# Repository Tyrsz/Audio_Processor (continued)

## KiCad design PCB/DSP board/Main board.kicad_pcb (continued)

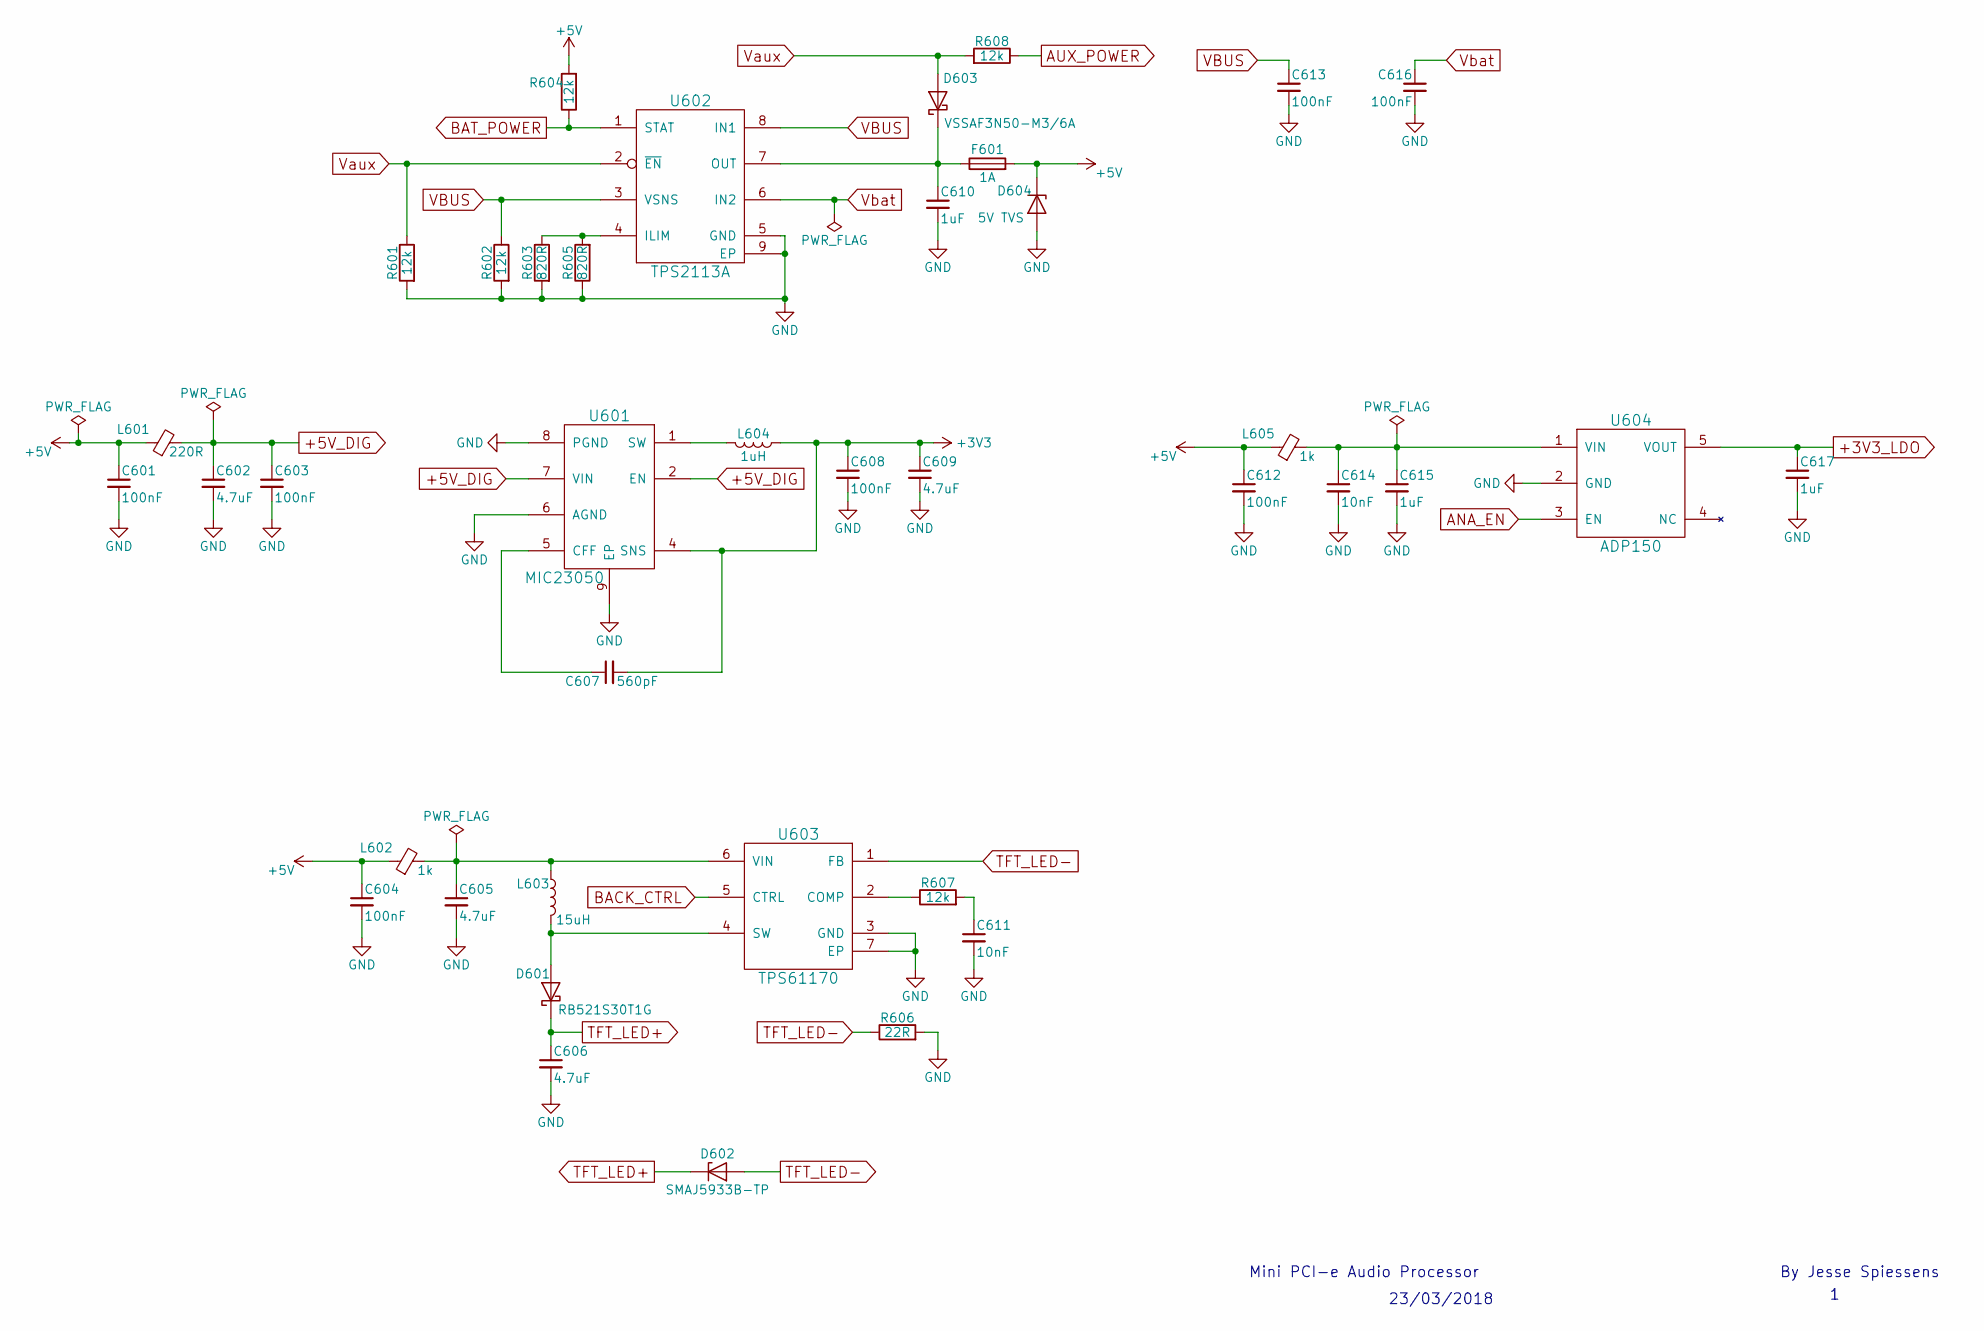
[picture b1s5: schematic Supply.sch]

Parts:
C601, C603, C604, C608, C612, C613, C616: 100nF; C_0603
C602, C605, C609: 4.7uF; C_0805
C606: 4.7uF; C_1206
C607: 560pF; C_0603
C610, C615, C617: 1uF; C_0603
C611, C614: 10nF; C_0603
D601: RB521S30T1G; D_SOD-523
D602: SMAJ5933B-TP; D_SMA
D603: VSSAF3N50-M3/6A; D_SMA
D604: 5V TVS; SOD-323F-2
F601: 1A; R_0603
L601: 220R; L_0603
L602, L605: 1k; L_0603
L603: 15uH; L_0805
L604: 1uH; L_0805
R601, R602, R604, R607, R608: 12k; R_0603
R603, R605: 820R; R_0603
R606: 22R; R_0805
U601: MIC23050; DFN-8-1EP_2x2mm_Pitch0.5mm
U602: TPS2113A; DFN-8-1EP_3x3mm_Pitch0.65mm
U603: TPS61170; DFN-6-1EP_2x2mm_Pitch0.65mm
U604: ADP150; TSOP-5_1.65x3.05mm_Pitch0.95mm

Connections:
+3V3: C607.2, C608.1, C609.1, L604.1, U601.4 (SNS); also elsewhere on the board
+3V3_LDO: C617.1, U604.5 (VOUT); also elsewhere on the board
+5V: C601.1, C604.1, C612.1, D604.1 (K), F601.2, L601.1, L602.1, L605.1, R604.2; also elsewhere on the board
+5V_DIG: C602.1, C603.1, L601.2, U601.2 (EN), U601.7 (VIN)
ANA_EN: U604.3 (EN); also elsewhere on the board
AUX_POWER: R608.1; also elsewhere on the board
BACK_CTRL: U603.5 (CTRL); also elsewhere on the board
BAT_POWER: R604.1, U602.1 (STAT); also elsewhere on the board
GND: C601.2, C602.2, C603.2, C604.2, C605.2, C606.2, C608.2, C609.2, C610.2, C611.2, C612.2, C613.2, C614.2, C615.2, C616.2, C617.2, D604.2 (A), R601.2, R602.2, R603.2, R605.1, R606.2, U601.6 (AGND), U601.8 (PGND), U601.9 (EP), U602.5 (GND), U602.9 (EP), U603.3 (GND), U603.7 (EP), U604.2 (GND); also elsewhere on the board
unnamed: C605.1, L602.2, L603.1, U603.6 (VIN)
unnamed: C607.1, U601.5 (CFF)
unnamed: C610.1, D603.1 (K), F601.1, U602.7 (OUT)
unnamed: C611.1, R607.2
unnamed: C614.1, C615.1, L605.2, U604.1 (VIN)
unnamed: D601.2 (A), L603.2, U603.4 (SW)
unnamed: L604.2, U601.1 (SW)
unnamed: R603.1, R605.2, U602.4 (ILIM)
unnamed: R607.1, U603.2 (COMP)
TFT_LED+: C606.1, D601.1 (K), D602.1 (K); also elsewhere on the board
TFT_LED-: D602.2 (A), R606.1, U603.1 (FB); also elsewhere on the board
VBUS: C613.1, R602.1, U602.3 (VSNS), U602.8 (IN1); also elsewhere on the board
Vaux: D603.2 (A), R601.1, R608.2, U602.2 (~EN); also elsewhere on the board
Vbat: C616.1, U602.6 (IN2); also elsewhere on the board

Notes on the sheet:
23/03/2018
Mini PCI-e Audio Processor
By Jesse Spiessens

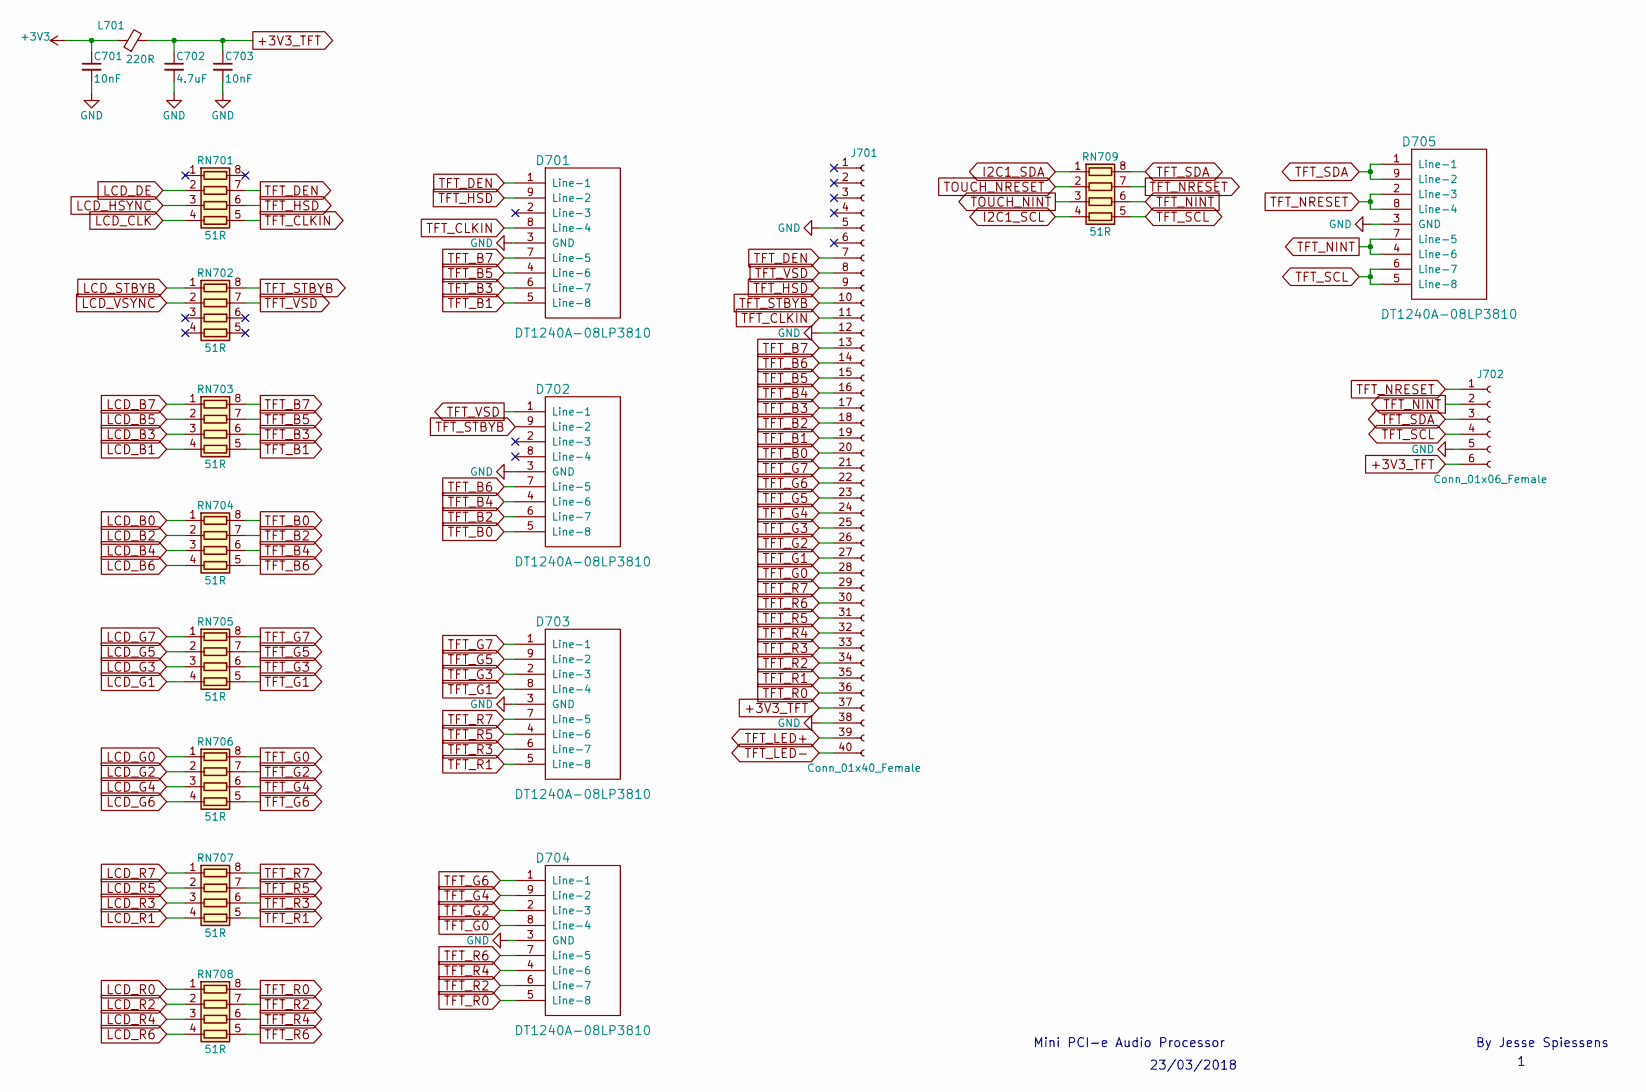
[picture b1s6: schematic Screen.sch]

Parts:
C701, C703: 10nF; C_0603
C702: 4.7uF; C_0805
D701, D702, D703, D704, D705: DT1240A-08LP3810; U-DFN3810-9
J701: Conn_01x40_Female; 78127-1408
J702: Conn_01x06_Female; 52808-0671
L701: 220R; L_0603
RN701, RN702, RN703, RN704, RN705, RN706, RN707, RN708, RN709: 51R; 0603_RN4

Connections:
+3V3: C701.1, L701.1; also elsewhere on the board
+3V3_TFT: C702.1, C703.1, J701.37, J702.6, L701.2
GND: C701.2, C702.2, C703.2, D701.3 (GND), D702.3 (GND), D703.3 (GND), D704.3 (GND), D705.3 (GND), J701.5, J701.12, J701.38, J702.5; also elsewhere on the board
I2C1_SCL: RN709.4 (R4.1); also elsewhere on the board
I2C1_SDA: RN709.1 (R1.1); also elsewhere on the board
LCD_B0: RN704.1 (R1.1); also elsewhere on the board
LCD_B1: RN703.4 (R4.1); also elsewhere on the board
LCD_B2: RN704.2 (R2.1); also elsewhere on the board
LCD_B3: RN703.3 (R3.1); also elsewhere on the board
LCD_B4: RN704.3 (R3.1); also elsewhere on the board
LCD_B5: RN703.2 (R2.1); also elsewhere on the board
LCD_B6: RN704.4 (R4.1); also elsewhere on the board
LCD_B7: RN703.1 (R1.1); also elsewhere on the board
LCD_CLK: RN701.4 (R4.1); also elsewhere on the board
LCD_DE: RN701.2 (R2.1); also elsewhere on the board
LCD_G0: RN706.1 (R1.1); also elsewhere on the board
LCD_G1: RN705.4 (R4.1); also elsewhere on the board
LCD_G2: RN706.2 (R2.1); also elsewhere on the board
LCD_G3: RN705.3 (R3.1); also elsewhere on the board
LCD_G4: RN706.3 (R3.1); also elsewhere on the board
LCD_G5: RN705.2 (R2.1); also elsewhere on the board
LCD_G6: RN706.4 (R4.1); also elsewhere on the board
LCD_G7: RN705.1 (R1.1); also elsewhere on the board
LCD_HSYNC: RN701.3 (R3.1); also elsewhere on the board
LCD_R0: RN708.1 (R1.1); also elsewhere on the board
LCD_R1: RN707.4 (R4.1); also elsewhere on the board
LCD_R2: RN708.2 (R2.1); also elsewhere on the board
LCD_R3: RN707.3 (R3.1); also elsewhere on the board
LCD_R4: RN708.3 (R3.1); also elsewhere on the board
LCD_R5: RN707.2 (R2.1); also elsewhere on the board
LCD_R6: RN708.4 (R4.1); also elsewhere on the board
LCD_R7: RN707.1 (R1.1); also elsewhere on the board
LCD_STBYB: RN702.1 (R1.1); also elsewhere on the board
LCD_VSYNC: RN702.2 (R2.1); also elsewhere on the board
TFT_B0: D702.5 (Line-8), J701.20, RN704.8 (R1.2)
TFT_B1: D701.5 (Line-8), J701.19, RN703.5 (R4.2)
TFT_B2: D702.6 (Line-7), J701.18, RN704.7 (R2.2)
TFT_B3: D701.6 (Line-7), J701.17, RN703.6 (R3.2)
TFT_B4: D702.4 (Line-6), J701.16, RN704.6 (R3.2)
TFT_B5: D701.4 (Line-6), J701.15, RN703.7 (R2.2)
TFT_B6: D702.7 (Line-5), J701.14, RN704.5 (R4.2)
TFT_B7: D701.7 (Line-5), J701.13, RN703.8 (R1.2)
TFT_CLKIN: D701.8 (Line-4), J701.11, RN701.5 (R4.2)
TFT_DEN: D701.1 (Line-1), J701.7, RN701.7 (R2.2)
TFT_G0: D704.8 (Line-4), J701.28, RN706.8 (R1.2)
TFT_G1: D703.8 (Line-4), J701.27, RN705.5 (R4.2)
TFT_G2: D704.2 (Line-3), J701.26, RN706.7 (R2.2)
TFT_G3: D703.2 (Line-3), J701.25, RN705.6 (R3.2)
TFT_G4: D704.9 (Line-2), J701.24, RN706.6 (R3.2)
TFT_G5: D703.9 (Line-2), J701.23, RN705.7 (R2.2)
TFT_G6: D704.1 (Line-1), J701.22, RN706.5 (R4.2)
TFT_G7: D703.1 (Line-1), J701.21, RN705.8 (R1.2)
TFT_HSD: D701.9 (Line-2), J701.9, RN701.6 (R3.2)
TFT_LED+: J701.39; also elsewhere on the board
TFT_LED-: J701.40; also elsewhere on the board
TFT_NINT: D705.4 (Line-6), D705.7 (Line-5), J702.2, RN709.6 (R3.2)
TFT_NRESET: D705.2 (Line-3), D705.8 (Line-4), J702.1, RN709.7 (R2.2)
TFT_R0: D704.5 (Line-8), J701.36, RN708.8 (R1.2)
TFT_R1: D703.5 (Line-8), J701.35, RN707.5 (R4.2)
TFT_R2: D704.6 (Line-7), J701.34, RN708.7 (R2.2)
TFT_R3: D703.6 (Line-7), J701.33, RN707.6 (R3.2)
TFT_R4: D704.4 (Line-6), J701.32, RN708.6 (R3.2)
TFT_R5: D703.4 (Line-6), J701.31, RN707.7 (R2.2)
TFT_R6: D704.7 (Line-5), J701.30, RN708.5 (R4.2)
TFT_R7: D703.7 (Line-5), J701.29, RN707.8 (R1.2)
TFT_SCL: D705.5 (Line-8), D705.6 (Line-7), J702.4, RN709.5 (R4.2)
TFT_SDA: D705.1 (Line-1), D705.9 (Line-2), J702.3, RN709.8 (R1.2)
TFT_STBYB: D702.9 (Line-2), J701.10, RN702.8 (R1.2)
TFT_VSD: D702.1 (Line-1), J701.8, RN702.7 (R2.2)
TOUCH_NINT: RN709.3 (R3.1); also elsewhere on the board
TOUCH_NRESET: RN709.2 (R2.1); also elsewhere on the board

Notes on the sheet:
23/03/2018
Mini PCI-e Audio Processor
By Jesse Spiessens

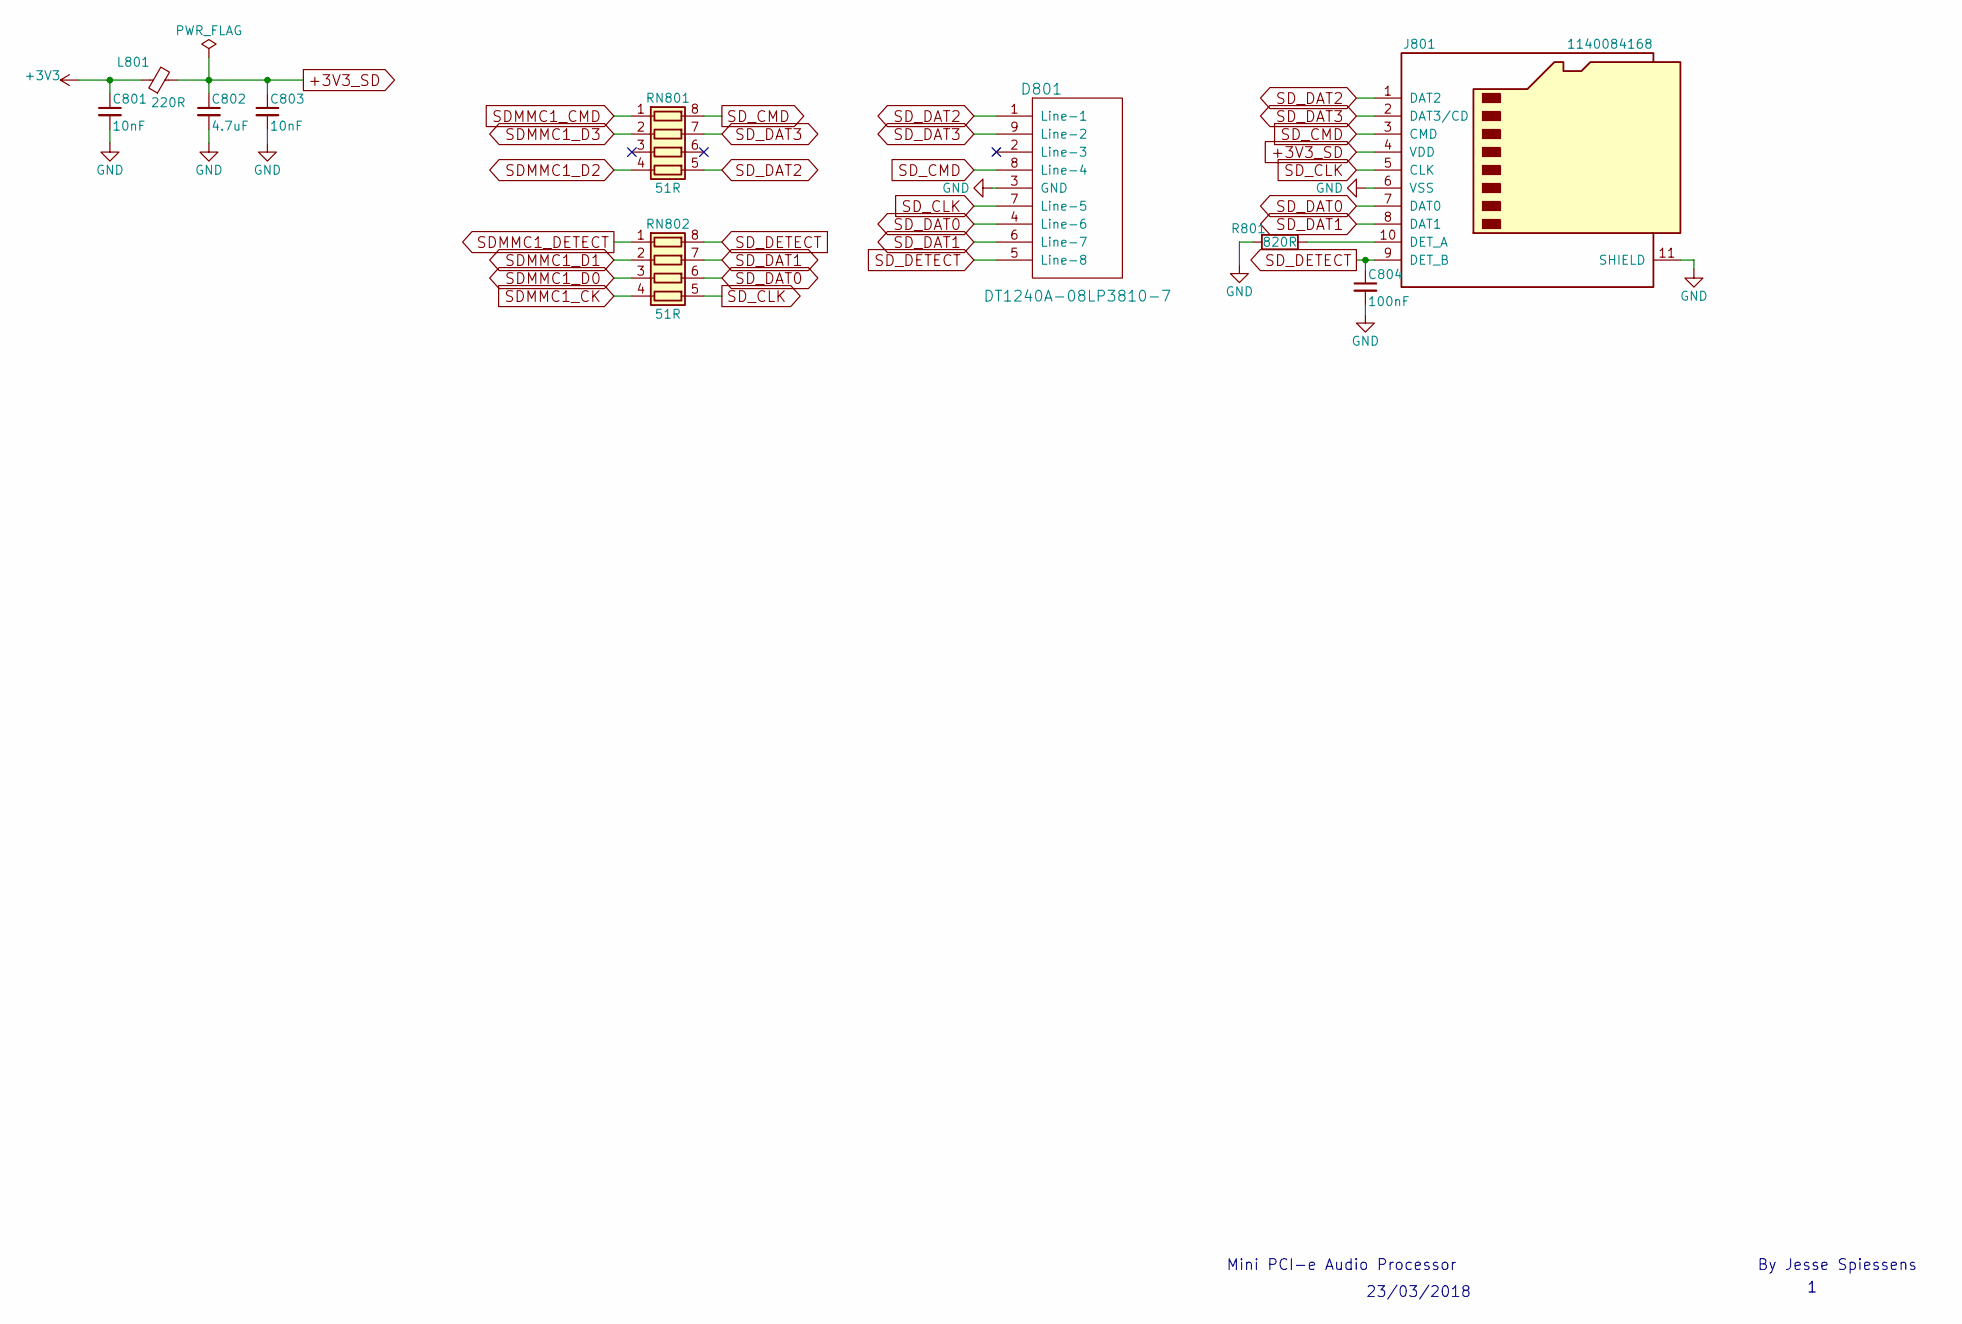
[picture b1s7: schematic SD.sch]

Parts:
C801, C803: 10nF; C_0603
C802: 4.7uF; C_0805
C804: 100nF; C_0603
D801: DT1240A-08LP3810-7; U-DFN3810-9
J801: 1140084168
L801: 220R; L_0603
R801: 820R; R_0603
RN801, RN802: 51R; 0603_RN4

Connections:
+3V3: C801.1, L801.1; also elsewhere on the board
+3V3_SD: C802.1, C803.1, J801.4 (VDD), L801.2
GND: C801.2, C802.2, C803.2, C804.2, D801.3 (GND), J801.6 (VSS), J801.11 (SHIELD), R801.2; also elsewhere on the board
unnamed: J801.10 (DET_A), R801.1
SDMMC1_CK: RN802.4 (R4.1); also elsewhere on the board
SDMMC1_CMD: RN801.1 (R1.1); also elsewhere on the board
SDMMC1_D0: RN802.3 (R3.1); also elsewhere on the board
SDMMC1_D1: RN802.2 (R2.1); also elsewhere on the board
SDMMC1_D2: RN801.4 (R4.1); also elsewhere on the board
SDMMC1_D3: RN801.2 (R2.1); also elsewhere on the board
SDMMC1_DETECT: RN802.1 (R1.1); also elsewhere on the board
SD_CLK: D801.7 (Line-5), J801.5 (CLK), RN802.5 (R4.2)
SD_CMD: D801.8 (Line-4), J801.3 (CMD), RN801.8 (R1.2)
SD_DAT0: D801.4 (Line-6), J801.7 (DAT0), RN802.6 (R3.2)
SD_DAT1: D801.6 (Line-7), J801.8 (DAT1), RN802.7 (R2.2)
SD_DAT2: D801.1 (Line-1), J801.1 (DAT2), RN801.5 (R4.2)
SD_DAT3: D801.9 (Line-2), J801.2 (DAT3/CD), RN801.7 (R2.2)
SD_DETECT: C804.1, D801.5 (Line-8), J801.9 (DET_B), RN802.8 (R1.2)

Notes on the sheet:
23/03/2018
Mini PCI-e Audio Processor
By Jesse Spiessens

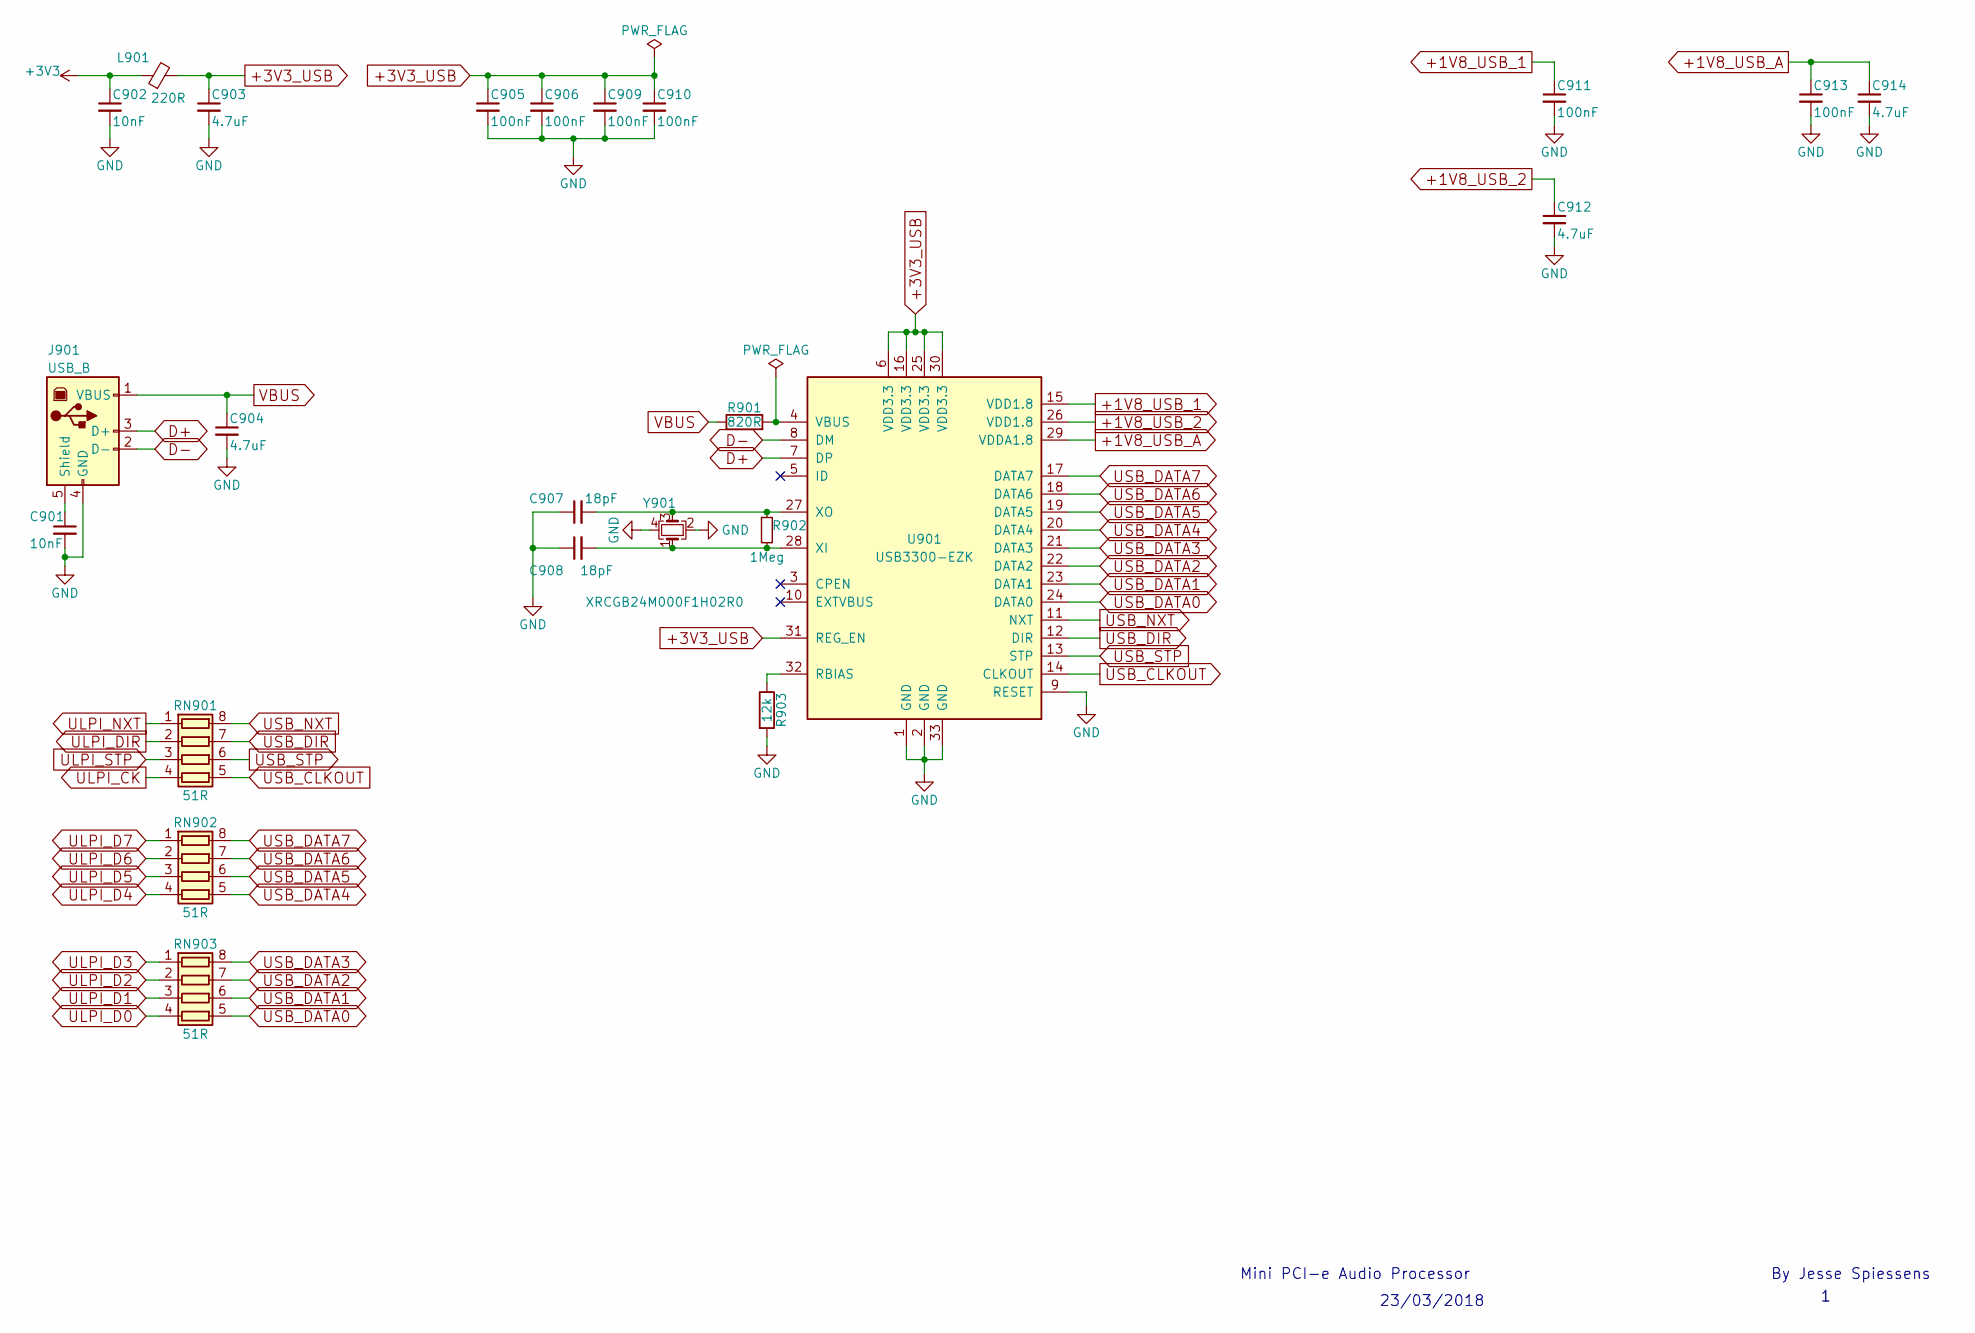
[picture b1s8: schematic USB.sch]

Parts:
C901, C902: 10nF; C_0603
C903, C904, C912, C914: 4.7uF; C_0805
C905, C906, C909, C910, C911, C913: 100nF; C_0603
C907, C908: 18pF; C_0603
J901: USB_B; USB_B_2.0
L901: 220R; L_0603
R901: 820R; R_0603
R902: 1Meg; R_0603
R903: 12k; R_0603
RN901, RN902, RN903: 51R; 0603_RN4
U901: USB3300-EZK; QFN-32-1EP_5x5mm_Pitch0.5mm
Y901: XRCGB24M000F1H02R0; Crystal_SMD_2016-4pin_2.0x1.6mm

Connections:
+1V8_USB_1: C911.1, U901.15 (VDD1.8)
+1V8_USB_2: C912.1, U901.26 (VDD1.8)
+1V8_USB_A: C913.1, C914.1, U901.29 (VDDA1.8)
+3V3: C902.1, L901.1; also elsewhere on the board
+3V3_USB: C903.1, C905.1, C906.1, C909.1, C910.1, L901.2, U901.6 (VDD3.3), U901.16 (VDD3.3), U901.25 (VDD3.3), U901.30 (VDD3.3), U901.31 (REG_EN)
D+: J901.3 (D+), U901.7 (DP); also elsewhere on the board
D-: J901.2 (D-), U901.8 (DM); also elsewhere on the board
GND: C901.2, C902.2, C903.2, C904.2, C905.2, C906.2, C907.1, C908.1, C909.2, C910.2, C911.2, C912.2, C913.2, C914.2, J901.4 (GND), R903.2, U901.1 (GND), U901.2 (GND), U901.9 (RESET), U901.33 (GND), Y901.2, Y901.4; also elsewhere on the board
unnamed: C901.1, J901.5 (Shield)
unnamed: C907.2, R902.1, U901.27 (XO), Y901.3
unnamed: C908.2, R902.2, U901.28 (XI), Y901.1
unnamed: R901.2, U901.4 (VBUS)
unnamed: R903.1, U901.32 (RBIAS)
ULPI_CK: RN901.4 (R4.1); also elsewhere on the board
ULPI_D0: RN903.4 (R4.1); also elsewhere on the board
ULPI_D1: RN903.3 (R3.1); also elsewhere on the board
ULPI_D2: RN903.2 (R2.1); also elsewhere on the board
ULPI_D3: RN903.1 (R1.1); also elsewhere on the board
ULPI_D4: RN902.4 (R4.1); also elsewhere on the board
ULPI_D5: RN902.3 (R3.1); also elsewhere on the board
ULPI_D6: RN902.2 (R2.1); also elsewhere on the board
ULPI_D7: RN902.1 (R1.1); also elsewhere on the board
ULPI_DIR: RN901.2 (R2.1); also elsewhere on the board
ULPI_NXT: RN901.1 (R1.1); also elsewhere on the board
ULPI_STP: RN901.3 (R3.1); also elsewhere on the board
USB_CLKOUT: RN901.5 (R4.2), U901.14 (CLKOUT)
USB_DATA0: RN903.5 (R4.2), U901.24 (DATA0)
USB_DATA1: RN903.6 (R3.2), U901.23 (DATA1)
USB_DATA2: RN903.7 (R2.2), U901.22 (DATA2)
USB_DATA3: RN903.8 (R1.2), U901.21 (DATA3)
USB_DATA4: RN902.5 (R4.2), U901.20 (DATA4)
USB_DATA5: RN902.6 (R3.2), U901.19 (DATA5)
USB_DATA6: RN902.7 (R2.2), U901.18 (DATA6)
USB_DATA7: RN902.8 (R1.2), U901.17 (DATA7)
USB_DIR: RN901.7 (R2.2), U901.12 (DIR)
USB_NXT: RN901.8 (R1.2), U901.11 (NXT)
USB_STP: RN901.6 (R3.2), U901.13 (STP)
VBUS: C904.1, J901.1 (VBUS), R901.1; also elsewhere on the board

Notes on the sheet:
23/03/2018
Mini PCI-e Audio Processor
By Jesse Spiessens

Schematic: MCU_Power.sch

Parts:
C301, C304, C305, C306, C311, C312, C313, C314, C319, C320, C321, C326, C327, C332, C333, C334: 1uF; C_0603
C302, C307, C308, C309, C315, C316, C317, C318, C322, C323, C324, C329, C330, C335, C336, C337: 10nF; C_0603
C303, C331: 100nF; C_0603
C310: 4.7uF; C_0805
C338, C339: 2.2uF; C_0603
L301: 220R; L_0603
L302: 1k; L_0603
U201: STM32H743II; LQFP-176_24x24mm_Pitch0.5mm

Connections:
+3V3: C301.1, C302.1, C303.1, L301.1, L302.1; also elsewhere on the board
+3V3_MCU: C304.1, C305.1, C306.1, C307.1, C308.1, C309.1, C310.1, C312.1, C313.1, C314.1, C316.1, C317.1, C318.1, C319.1, C320.1, C321.1, C322.1, C323.1, C324.1, C326.1, C327.1, C329.1, C330.1, C331.1, C332.1, C333.1, C334.1, C335.1, C336.1, C337.1, L301.2, U201.15 (VDD), U201.23 (VDD), U201.36 (VDD), U201.49 (VDD), U201.62 (VDD), U201.72 (VDD), U201.82 (VDD), U201.91 (VDD), U201.103 (VDD), U201.114 (VDD33USB), U201.127 (VDD), U201.136 (VDD), U201.149 (VDD), U201.159 (VDD), U201.172 (VDD); also elsewhere on the board
GND: C301.2, C302.2, C303.2, C304.2, C305.2, C306.2, C307.2, C308.2, C309.2, C310.2, C311.2, C312.2, C313.2, C314.2, C315.2, C316.2, C317.2, C318.2, C319.2, C320.2, C321.2, C322.2, C323.2, C324.2, C326.2, C327.2, C329.2, C330.2, C331.2, C332.2, C333.2, C334.2, C335.2, C336.2, C337.2, C338.2, C339.2, U201.14 (VSS), U201.22 (VSS), U201.37 (VSSA), U201.48 (VSS), U201.61 (VSS), U201.71 (VSS), U201.90 (VSS), U201.102 (VSS), U201.113 (VSS), U201.126 (VSS), U201.135 (VSS), U201.148 (VSS), U201.158 (VSS); also elsewhere on the board
unnamed: C311.1, C315.1, L302.2, U201.38 (VREF+), U201.39 (VDDA)
unnamed: C338.1, U201.125 (VCAP2)
unnamed: C339.1, U201.81 (VCAP1)

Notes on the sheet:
23/03/2018
Mini PCI-e Audio Processor
By Jesse Spiessens

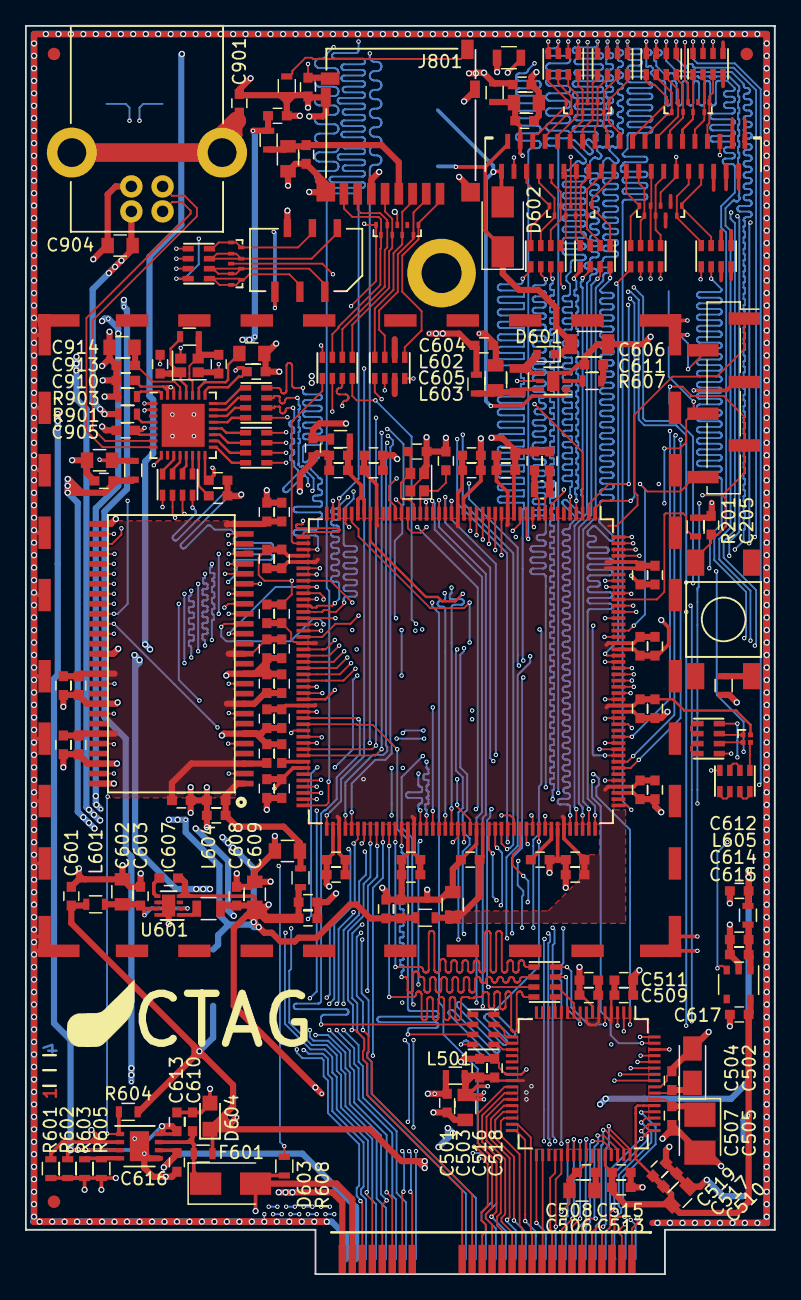
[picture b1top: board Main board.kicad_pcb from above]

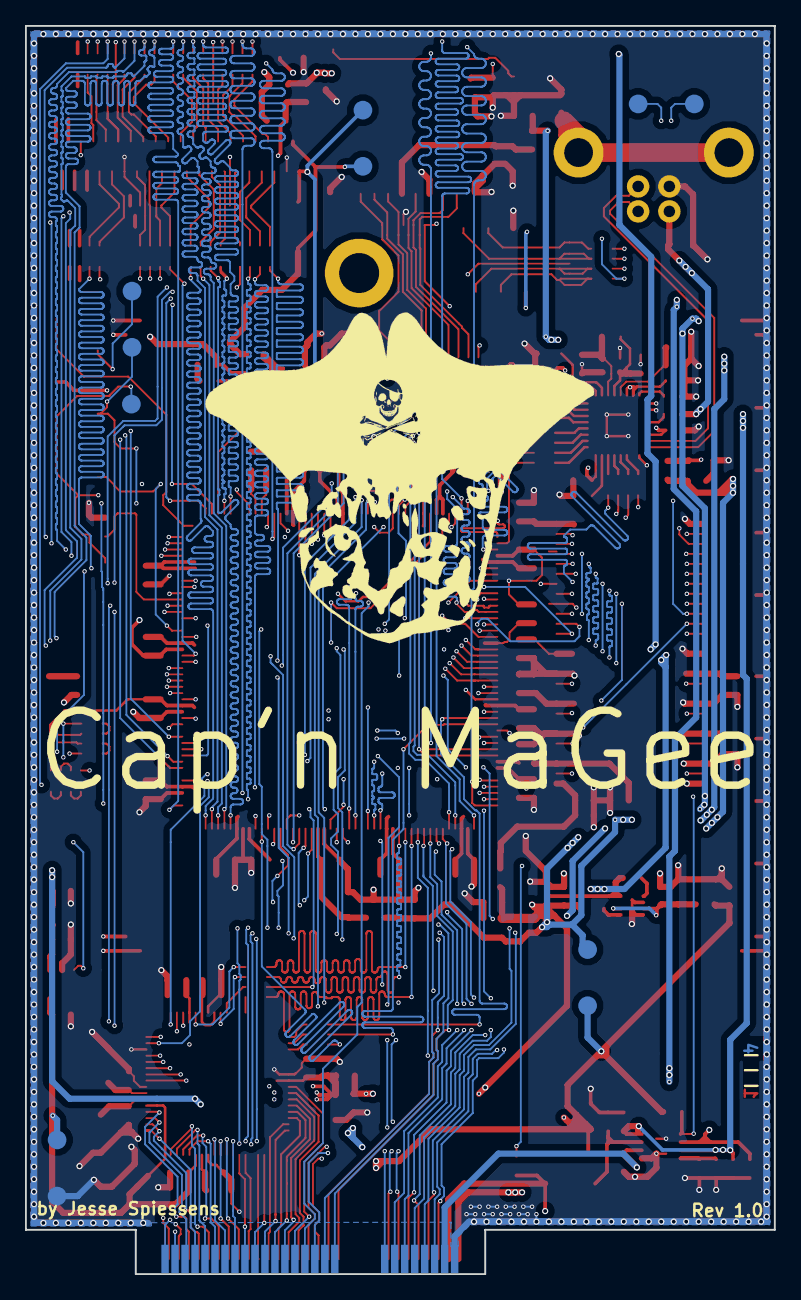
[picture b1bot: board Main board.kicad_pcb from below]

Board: 4 copper layers, 60.0 x 100.0 mm, 202 parts (11 on the bottom side), 269 nets.

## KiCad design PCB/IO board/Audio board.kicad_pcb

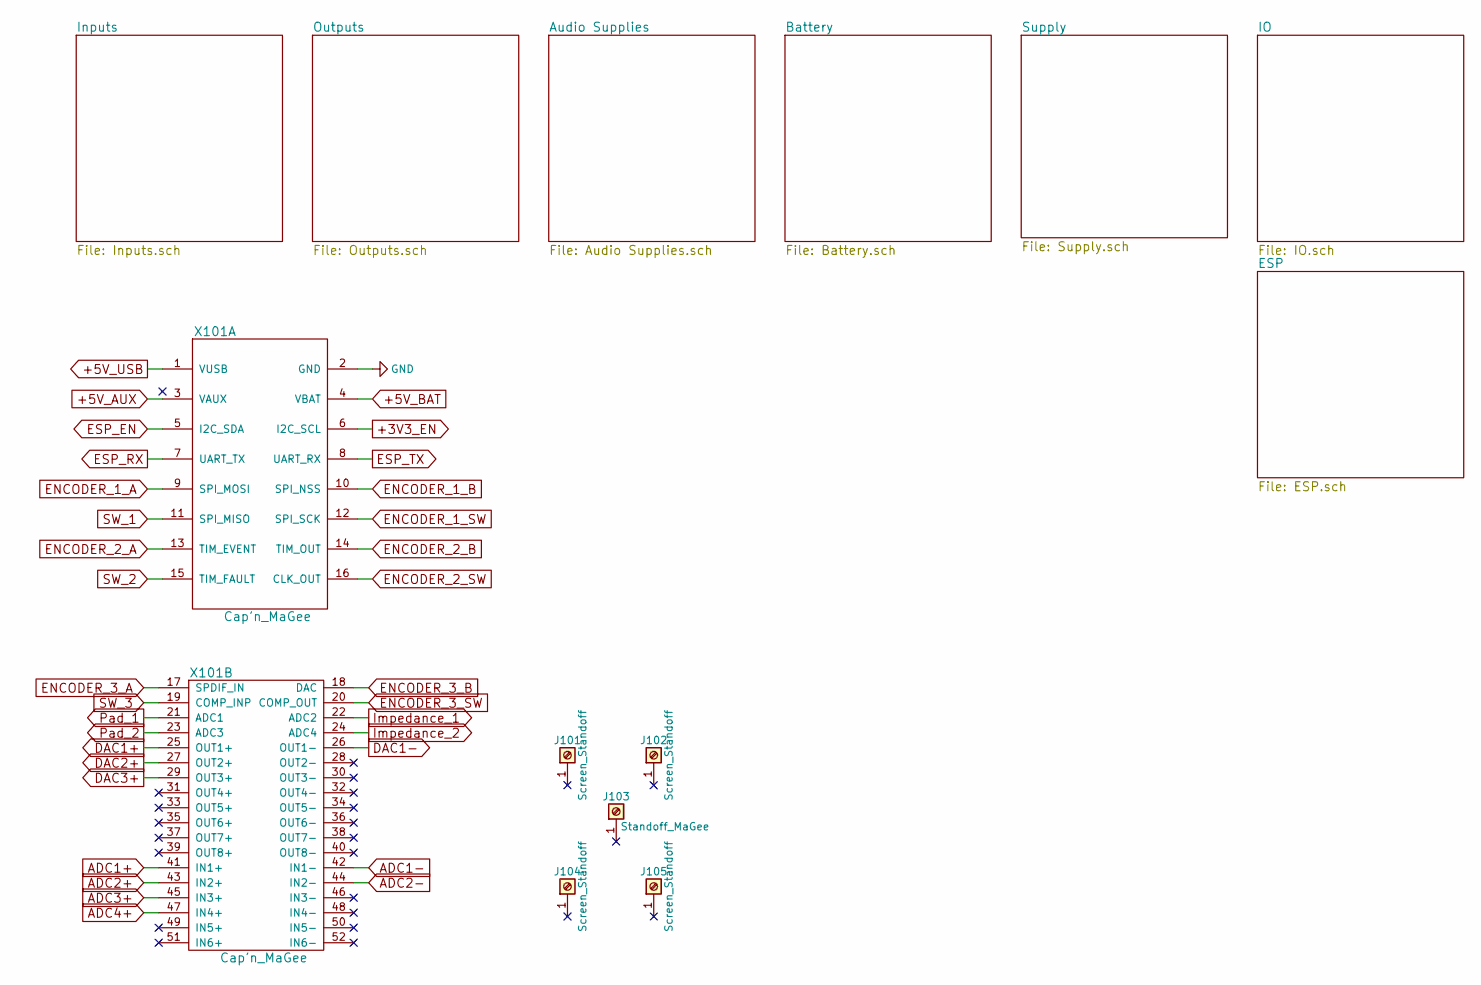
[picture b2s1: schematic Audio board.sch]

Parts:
J101, J102, J104, J105: Screen_Standoff; HARWIN_R30-1001002
J103: Standoff_MaGee; Keystone_1560A
X101: Cap'n_MaGee; Mini_PCI-e_Female

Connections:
+3V3_EN: X101.6 (I2C_SCL); also elsewhere on the board
+5V_AUX: X101.3 (VAUX); also elsewhere on the board
+5V_BAT: X101.4 (VBAT); also elsewhere on the board
+5V_USB: X101.1 (VUSB); also elsewhere on the board
ADC1+: X101.41 (IN1+); also elsewhere on the board
ADC1-: X101.42 (IN1-); also elsewhere on the board
ADC2+: X101.43 (IN2+); also elsewhere on the board
ADC2-: X101.44 (IN2-); also elsewhere on the board
ADC3+: X101.45 (IN3+); also elsewhere on the board
ADC4+: X101.47 (IN4+); also elsewhere on the board
DAC1+: X101.25 (OUT1+); also elsewhere on the board
DAC1-: X101.26 (OUT1-); also elsewhere on the board
DAC2+: X101.27 (OUT2+); also elsewhere on the board
DAC3+: X101.29 (OUT3+); also elsewhere on the board
ENCODER_1_A: X101.9 (SPI_MOSI); also elsewhere on the board
ENCODER_1_B: X101.10 (SPI_NSS); also elsewhere on the board
ENCODER_1_SW: X101.12 (SPI_SCK); also elsewhere on the board
ENCODER_2_A: X101.13 (TIM_EVENT); also elsewhere on the board
ENCODER_2_B: X101.14 (TIM_OUT); also elsewhere on the board
ENCODER_2_SW: X101.16 (CLK_OUT); also elsewhere on the board
ENCODER_3_A: X101.17 (SPDIF_IN); also elsewhere on the board
ENCODER_3_B: X101.18 (DAC); also elsewhere on the board
ENCODER_3_SW: X101.20 (COMP_OUT); also elsewhere on the board
ESP_EN: X101.5 (I2C_SDA); also elsewhere on the board
ESP_RX: X101.7 (UART_TX); also elsewhere on the board
ESP_TX: X101.8 (UART_RX); also elsewhere on the board
GND: X101.2 (GND); also elsewhere on the board
Impedance_1: X101.22 (ADC2); also elsewhere on the board
Impedance_2: X101.24 (ADC4); also elsewhere on the board
Pad_1: X101.21 (ADC1); also elsewhere on the board
Pad_2: X101.23 (ADC3); also elsewhere on the board
SW_1: X101.11 (SPI_MISO); also elsewhere on the board
SW_2: X101.15 (TIM_FAULT); also elsewhere on the board
SW_3: X101.19 (COMP_INP); also elsewhere on the board
